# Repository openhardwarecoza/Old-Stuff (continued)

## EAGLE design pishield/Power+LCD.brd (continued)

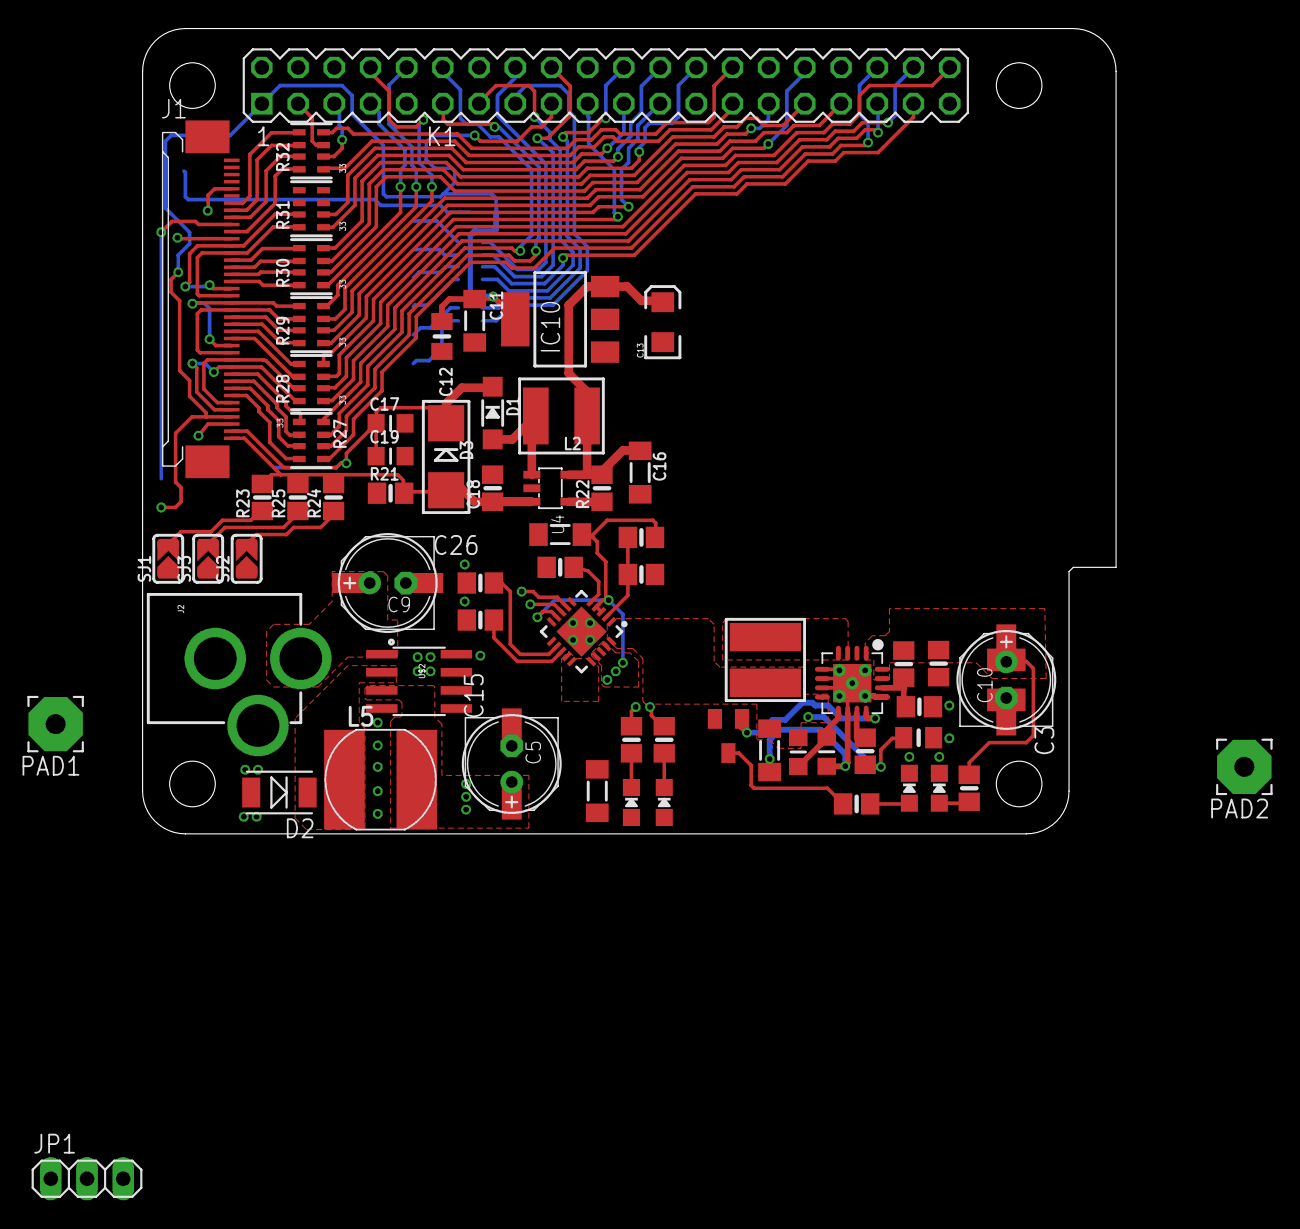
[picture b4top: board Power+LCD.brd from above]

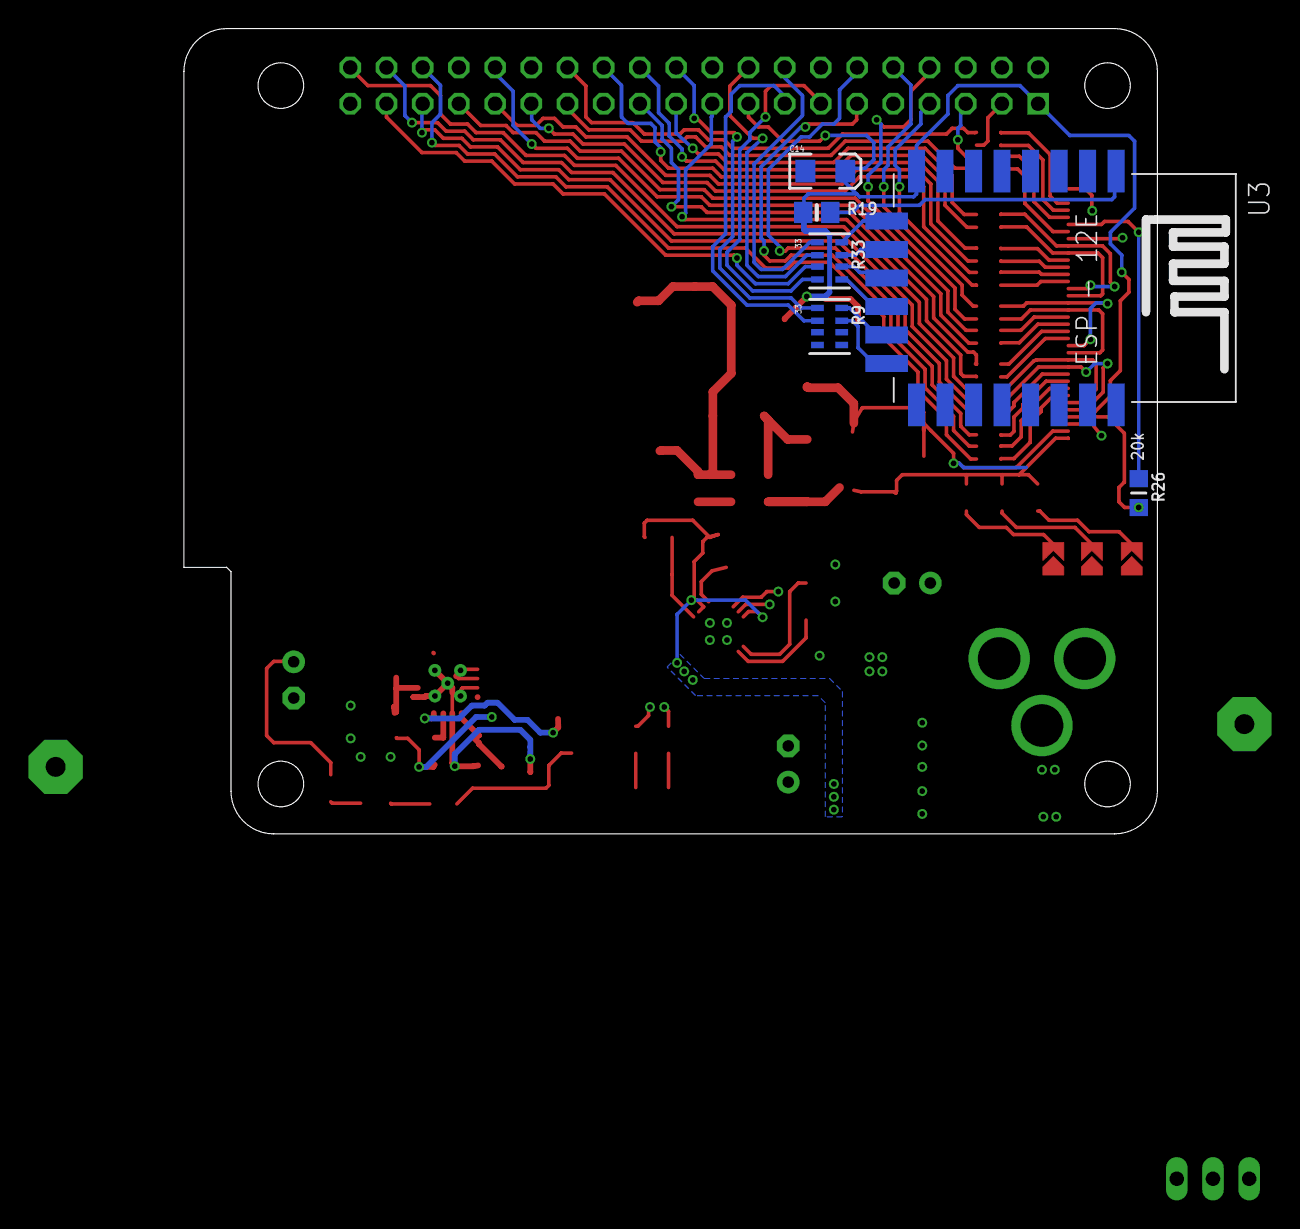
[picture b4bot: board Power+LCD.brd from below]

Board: 2 copper layers, 68.3 x 56.5 mm, 75 parts (6 on the bottom side), 90 nets.

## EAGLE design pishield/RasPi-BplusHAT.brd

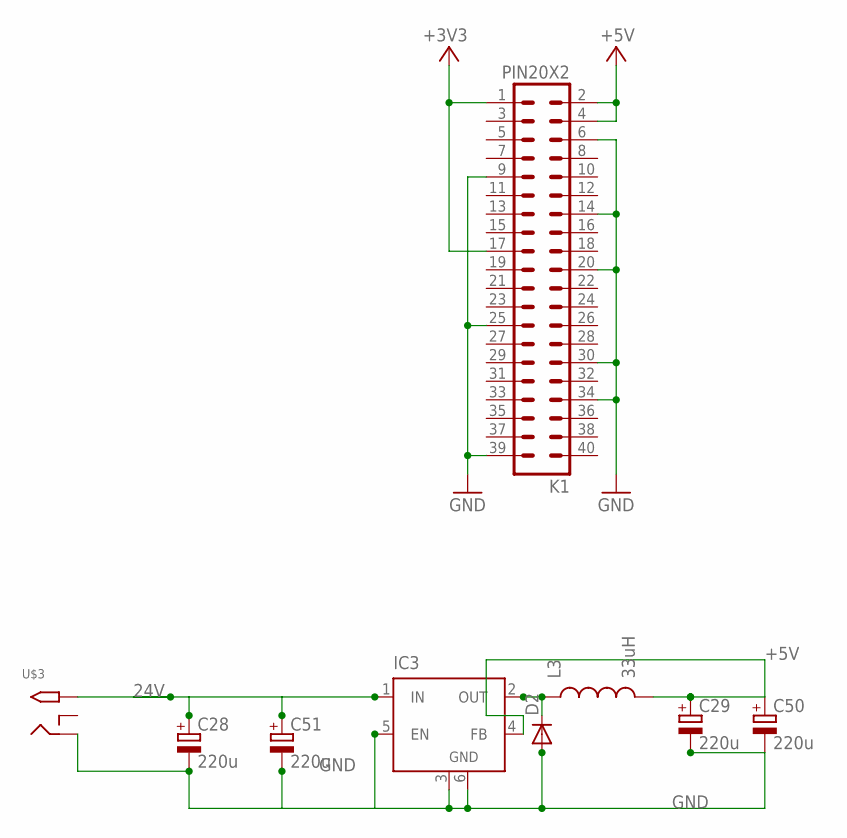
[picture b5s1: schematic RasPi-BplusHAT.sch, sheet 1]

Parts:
C28, C29: 220u; E2,5-7
C50, C51: 220u; PANASONIC_D
D2: DIODE-DO-214AC; DO-214AC
IC3: LM2596S; TO263-5
K1: PIN20X2; PIN_20X2
L3: 33uH; CDRH125
U$3: 2.1MMJACKTHM; PJ-102A

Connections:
24V: C28.+, C51.+, IC3.1 (IN), U$3.TIP
+3V3: K1.1, K1.17
+5V: C29.+, C50.+, IC3.4 (FB), K1.2, K1.4, L3.2
GND: C28.-, C29.-, C50.-, C51.-, D2.2 (A), IC3.3 (GND), IC3.5 (EN), IC3.6 (GND), K1.6, K1.9, K1.14, K1.20, K1.25, K1.30, K1.34, K1.39, U$3.RING
unnamed: D2.1 (C), IC3.2 (OUT), L3.1

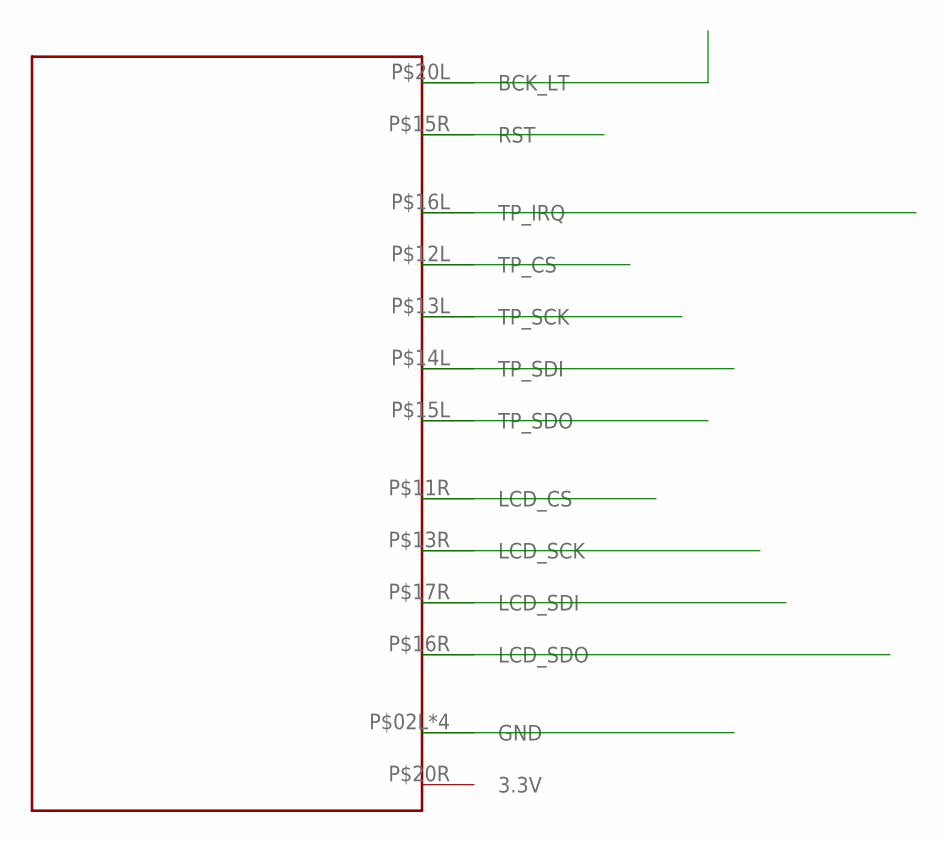
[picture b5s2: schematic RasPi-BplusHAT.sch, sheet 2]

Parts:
U$1: HY28BSTD; HY28B

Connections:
unnamed: U$1.P$02L (GND), U$1.P$02R (GND), U$1.P$19L (GND), U$1.P$19R (GND)

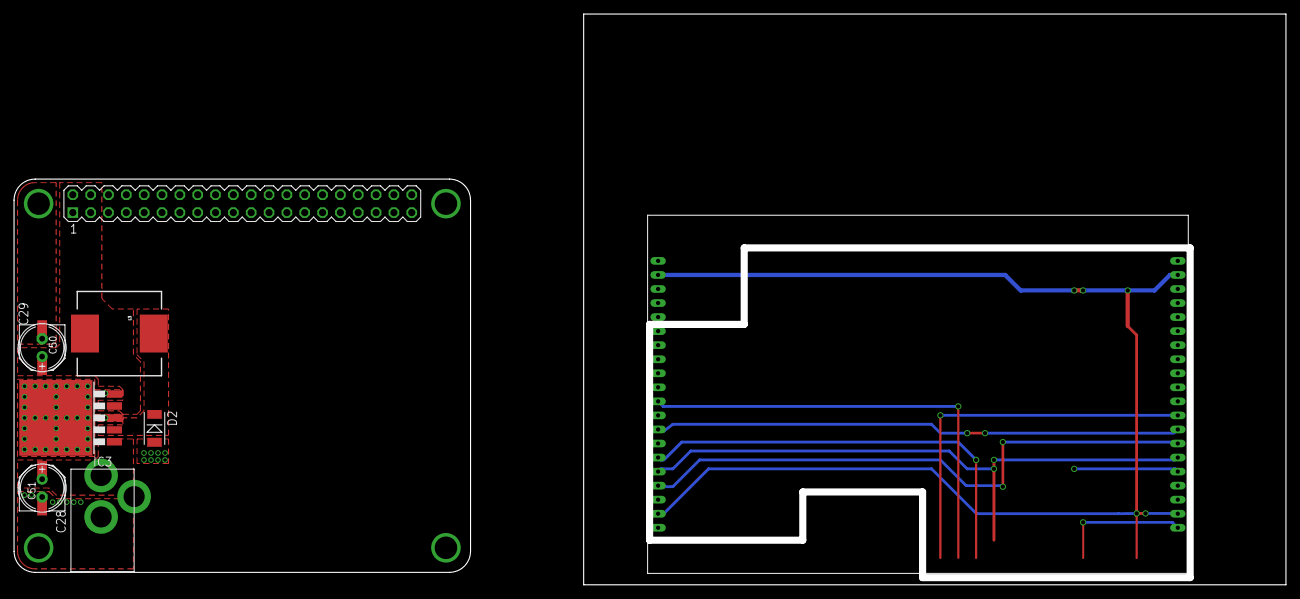
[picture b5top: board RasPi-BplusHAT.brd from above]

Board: 2 copper layers, 65.0 x 56.0 mm, 10 parts (0 on the bottom side), 6 nets.

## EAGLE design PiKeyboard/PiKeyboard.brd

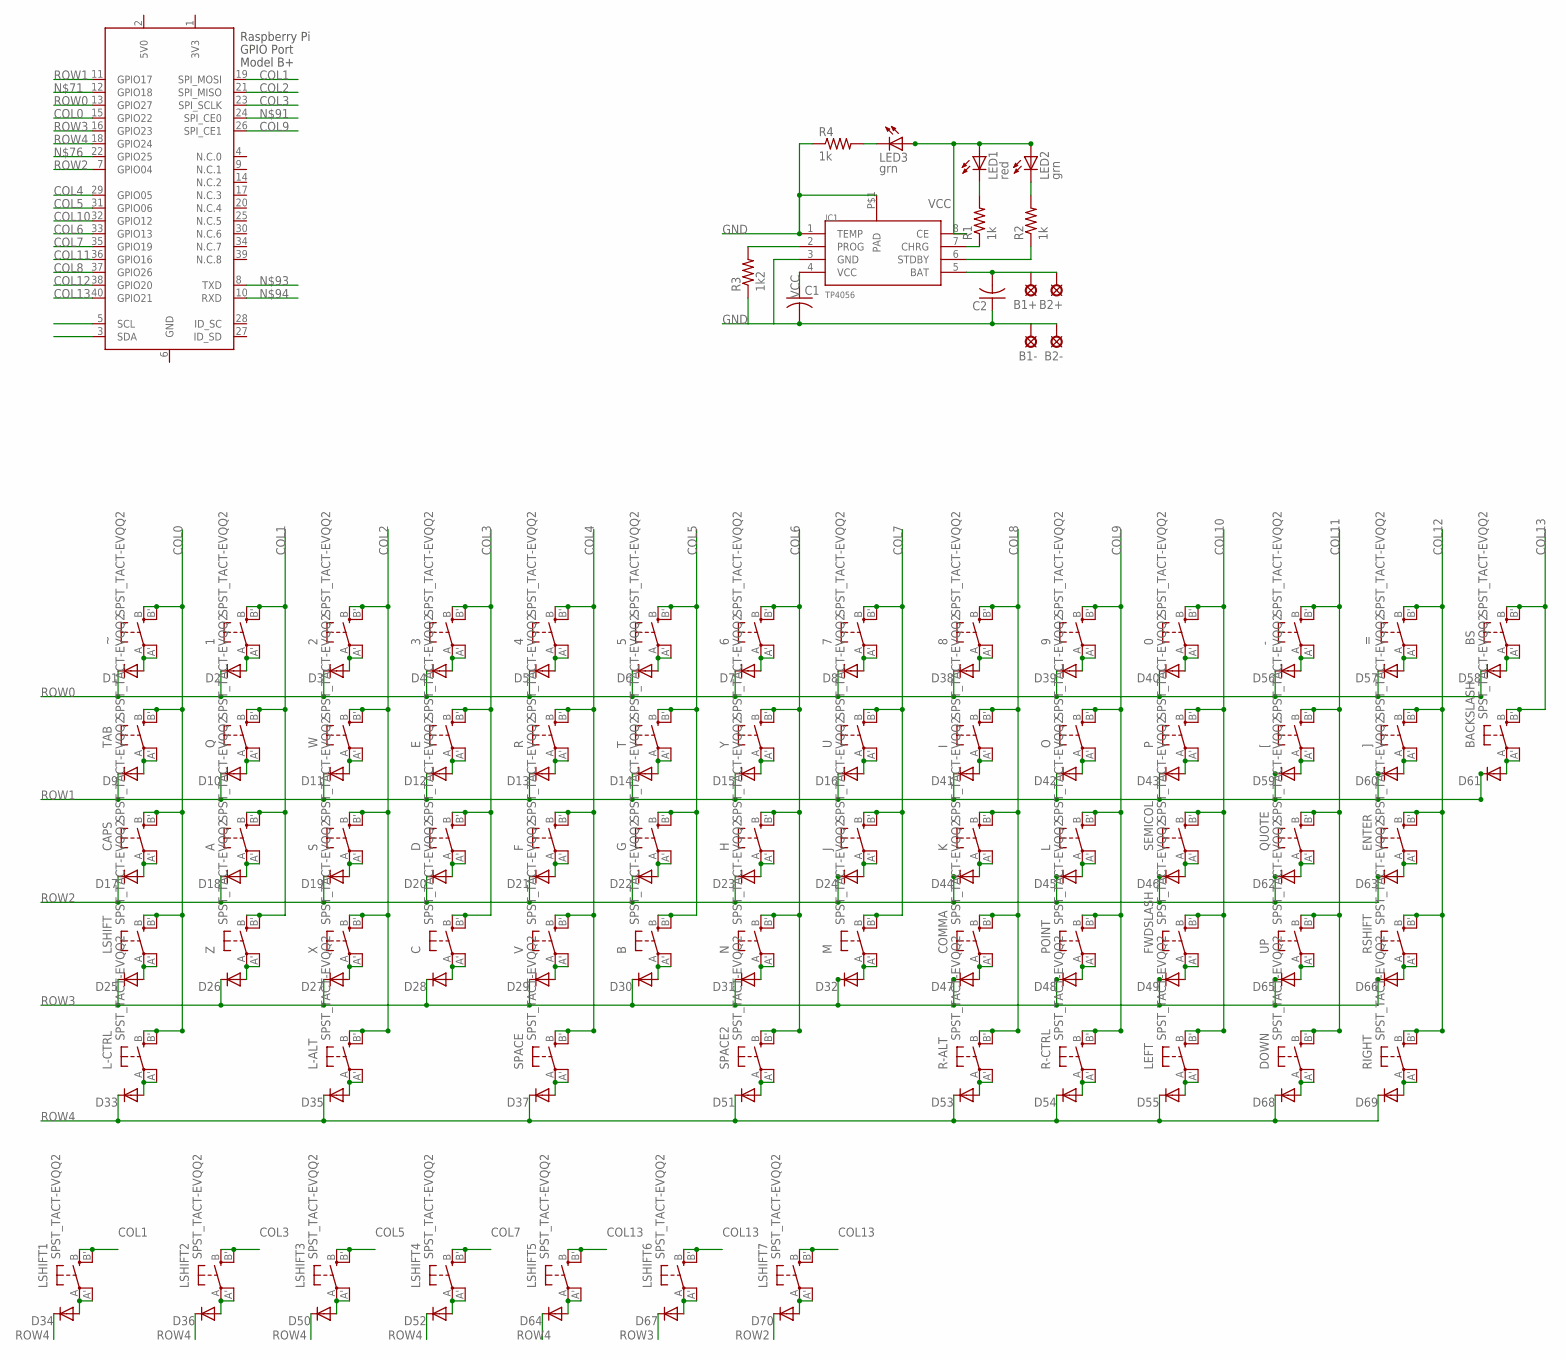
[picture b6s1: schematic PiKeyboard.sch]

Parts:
0, 1, 2, 3, 4, 5, 6, 7, 8, 9: SPST_TACT-EVQQ2; EVQ-Q2
-: SPST_TACT-EVQQ2; EVQ-Q2
=: SPST_TACT-EVQQ2; EVQ-Q2
A: SPST_TACT-EVQQ2; EVQ-Q2
B: SPST_TACT-EVQQ2; EVQ-Q2
B1+, B1-, B2+, B2-: SE14
BACKSLASH: SPST_TACT-EVQQ2; EVQ-Q2
BS: SPST_TACT-EVQQ2; EVQ-Q2
C: SPST_TACT-EVQQ2; EVQ-Q2
C1, C2: C-USC1206K; C1206K
CAPS: SPST_TACT-EVQQ2; EVQ-Q2
COMMA: SPST_TACT-EVQQ2; EVQ-Q2
D: SPST_TACT-EVQQ2; EVQ-Q2
D1, D2, D3, D4, D5, D6, D7, D8, D9, D10, D11, D12, D13, D14, D15, D16, D17, D18, D19, D20, D21, D22, D23, D24, D25, D26, D27, D28, D29, D30, D31, D32, D33, D34, D35, D36, D37, D38, D39, D40, D41, D42, D43, D44, D45, D46, D47, D48, D49, D50, D51, D52, D53, D54, D55, D56, D57, D58, D59, D60, D61, D62, D63, D64, D65, D66, D67, D68, D69, D70: DIODE-DO214AC; DO214AC
DOWN: SPST_TACT-EVQQ2; EVQ-Q2
E: SPST_TACT-EVQQ2; EVQ-Q2
ENTER: SPST_TACT-EVQQ2; EVQ-Q2
F: SPST_TACT-EVQQ2; EVQ-Q2
FWDSLASH: SPST_TACT-EVQQ2; EVQ-Q2
G: SPST_TACT-EVQQ2; EVQ-Q2
H: SPST_TACT-EVQQ2; EVQ-Q2
I: SPST_TACT-EVQQ2; EVQ-Q2
IC1: TP4056; SOP-8
J: SPST_TACT-EVQQ2; EVQ-Q2
K: SPST_TACT-EVQQ2; EVQ-Q2
L: SPST_TACT-EVQQ2; EVQ-Q2
L-ALT: SPST_TACT-EVQQ2; EVQ-Q2
L-CTRL: SPST_TACT-EVQQ2; EVQ-Q2
LED1: red; CHIPLED_1206
LED2, LED3: grn; CHIPLED_1206
LEFT: SPST_TACT-EVQQ2; EVQ-Q2
LSHIFT, LSHIFT1, LSHIFT2, LSHIFT3, LSHIFT4, LSHIFT5, LSHIFT6, LSHIFT7: SPST_TACT-EVQQ2; EVQ-Q2
M: SPST_TACT-EVQQ2; EVQ-Q2
N: SPST_TACT-EVQQ2; EVQ-Q2
O: SPST_TACT-EVQQ2; EVQ-Q2
P: SPST_TACT-EVQQ2; EVQ-Q2
POINT: SPST_TACT-EVQQ2; EVQ-Q2
Q: SPST_TACT-EVQQ2; EVQ-Q2
QUOTE: SPST_TACT-EVQQ2; EVQ-Q2
R: SPST_TACT-EVQQ2; EVQ-Q2
R1, R2, R4: 1k; M1206
R3: 1k2; M1206
R-ALT: SPST_TACT-EVQQ2; EVQ-Q2
R-CTRL: SPST_TACT-EVQQ2; EVQ-Q2
RIGHT: SPST_TACT-EVQQ2; EVQ-Q2
RSHIFT: SPST_TACT-EVQQ2; EVQ-Q2
S: SPST_TACT-EVQQ2; EVQ-Q2
SEMICOL: SPST_TACT-EVQQ2; EVQ-Q2
SPACE, SPACE2: SPST_TACT-EVQQ2; EVQ-Q2
T: SPST_TACT-EVQQ2; EVQ-Q2
TAB: SPST_TACT-EVQQ2; EVQ-Q2
U: SPST_TACT-EVQQ2; EVQ-Q2
UP: SPST_TACT-EVQQ2; EVQ-Q2
V: SPST_TACT-EVQQ2; EVQ-Q2
W: SPST_TACT-EVQQ2; EVQ-Q2
X: SPST_TACT-EVQQ2; EVQ-Q2
X1: RASPI_BOARD_B+_F; RASPI_BOARD_B+_FULL
Y: SPST_TACT-EVQQ2; EVQ-Q2
Z: SPST_TACT-EVQQ2; EVQ-Q2
[: SPST_TACT-EVQQ2; EVQ-Q2
]: SPST_TACT-EVQQ2; EVQ-Q2
~: SPST_TACT-EVQQ2; EVQ-Q2

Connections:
3V3: X1.1 (3V3)
5V0: X1.2 (5V0)
BATT+: B1+.MP, B2+.MP, C2.2, IC1.5 (BAT)
CHGLED: IC1.7 (CHRG), R1.1
CHRG: LED1.C, R1.2
COL0: CAPS.B (S), CAPS.B' (S1), L-CTRL.B (S), L-CTRL.B' (S1), LSHIFT.B (S), LSHIFT.B' (S1), TAB.B (S), TAB.B' (S1), X1.15 (GPIO22), ~.B (S), ~.B' (S1)
COL1: 1.B (S), 1.B' (S1), A.B (S), A.B' (S1), LSHIFT1.B (S), LSHIFT1.B' (S1), Q.B (S), Q.B' (S1), X1.19 (SPI_MOSI), Z.B (S), Z.B' (S1)
COL2: 2.B (S), 2.B' (S1), L-ALT.B (S), L-ALT.B' (S1), S.B (S), S.B' (S1), W.B (S), W.B' (S1), X.B (S), X.B' (S1), X1.21 (SPI_MISO)
COL3: 3.B (S), 3.B' (S1), C.B (S), C.B' (S1), D.B (S), D.B' (S1), E.B (S), E.B' (S1), LSHIFT2.B (S), LSHIFT2.B' (S1), X1.23 (SPI_SCLK)
COL4: 4.B (S), 4.B' (S1), F.B (S), F.B' (S1), R.B (S), R.B' (S1), SPACE.B (S), SPACE.B' (S1), V.B (S), V.B' (S1), X1.29 (GPIO05)
COL5: 5.B (S), 5.B' (S1), B.B (S), B.B' (S1), G.B (S), G.B' (S1), LSHIFT3.B (S), LSHIFT3.B' (S1), T.B (S), T.B' (S1), X1.31 (GPIO06)
COL6: 6.B (S), 6.B' (S1), H.B (S), H.B' (S1), N.B (S), N.B' (S1), SPACE2.B (S), SPACE2.B' (S1), X1.33 (GPIO13), Y.B (S), Y.B' (S1)
COL7: 7.B (S), 7.B' (S1), J.B (S), J.B' (S1), LSHIFT4.B (S), LSHIFT4.B' (S1), M.B (S), M.B' (S1), U.B (S), U.B' (S1), X1.35 (GPIO19)
COL8: 8.B (S), 8.B' (S1), COMMA.B (S), COMMA.B' (S1), I.B (S), I.B' (S1), K.B (S), K.B' (S1), R-ALT.B (S), R-ALT.B' (S1), X1.37 (GPIO26)
COL9: 9.B (S), 9.B' (S1), L.B (S), L.B' (S1), O.B (S), O.B' (S1), POINT.B (S), POINT.B' (S1), R-CTRL.B (S), R-CTRL.B' (S1), X1.26 (SPI_CE1)
COL10: 0.B (S), 0.B' (S1), FWDSLASH.B (S), FWDSLASH.B' (S1), LEFT.B (S), LEFT.B' (S1), P.B (S), P.B' (S1), SEMICOL.B (S), SEMICOL.B' (S1), X1.32 (GPIO12)
COL11: -.B (S), -.B' (S1), DOWN.B (S), DOWN.B' (S1), QUOTE.B (S), QUOTE.B' (S1), UP.B (S), UP.B' (S1), X1.36 (GPIO16), [.B (S), [.B' (S1)
COL12: =.B (S), =.B' (S1), ENTER.B (S), ENTER.B' (S1), RIGHT.B (S), RIGHT.B' (S1), RSHIFT.B (S), RSHIFT.B' (S1), X1.38 (GPIO20), ].B (S), ].B' (S1)
COL13: BACKSLASH.B (S), BACKSLASH.B' (S1), BS.B (S), BS.B' (S1), LSHIFT5.B (S), LSHIFT5.B' (S1), LSHIFT6.B (S), LSHIFT6.B' (S1), LSHIFT7.B (S), LSHIFT7.B' (S1), X1.40 (GPIO21)
GND: B1-.MP, B2-.MP, C1.2, C2.1, IC1.1 (TEMP), IC1.3 (GND), IC1.P$1 (PAD), R3.1, R4.1, X1.6 (GND)
unnamed: D1.A, ~.A, ~.A' (P1)
unnamed: 1.A, 1.A' (P1), D2.A
unnamed: 2.A, 2.A' (P1), D3.A
unnamed: 3.A, 3.A' (P1), D4.A
unnamed: 4.A, 4.A' (P1), D5.A
unnamed: 5.A, 5.A' (P1), D6.A
unnamed: 6.A, 6.A' (P1), D7.A
unnamed: 7.A, 7.A' (P1), D8.A
unnamed: D9.A, TAB.A, TAB.A' (P1)
unnamed: D10.A, Q.A, Q.A' (P1)
unnamed: D11.A, W.A, W.A' (P1)
unnamed: D12.A, E.A, E.A' (P1)
unnamed: D13.A, R.A, R.A' (P1)
unnamed: D14.A, T.A, T.A' (P1)
unnamed: D15.A, Y.A, Y.A' (P1)
unnamed: D16.A, U.A, U.A' (P1)
unnamed: CAPS.A, CAPS.A' (P1), D17.A
unnamed: A.A, A.A' (P1), D18.A
unnamed: D19.A, S.A, S.A' (P1)
unnamed: D.A, D.A' (P1), D20.A
unnamed: D21.A, F.A, F.A' (P1)
unnamed: D22.A, G.A, G.A' (P1)
unnamed: D23.A, H.A, H.A' (P1)
unnamed: D24.A, J.A, J.A' (P1)
unnamed: D25.A, LSHIFT.A, LSHIFT.A' (P1)
unnamed: D26.A, Z.A, Z.A' (P1)
unnamed: D27.A, X.A, X.A' (P1)
unnamed: C.A, C.A' (P1), D28.A
unnamed: D29.A, V.A, V.A' (P1)
unnamed: B.A, B.A' (P1), D30.A
unnamed: D31.A, N.A, N.A' (P1)
unnamed: D32.A, M.A, M.A' (P1)
unnamed: D33.A, L-CTRL.A, L-CTRL.A' (P1)
unnamed: D34.A, LSHIFT1.A, LSHIFT1.A' (P1)
unnamed: D36.A, LSHIFT2.A, LSHIFT2.A' (P1)
unnamed: D50.A, LSHIFT3.A, LSHIFT3.A' (P1)
unnamed: D37.A, SPACE.A, SPACE.A' (P1)
unnamed: 8.A, 8.A' (P1), D38.A
unnamed: 9.A, 9.A' (P1), D39.A
unnamed: 0.A, 0.A' (P1), D40.A
unnamed: D41.A, I.A, I.A' (P1)
unnamed: D42.A, O.A, O.A' (P1)
unnamed: D43.A, P.A, P.A' (P1)
unnamed: D44.A, K.A, K.A' (P1)
unnamed: D45.A, L.A, L.A' (P1)
unnamed: D46.A, SEMICOL.A, SEMICOL.A' (P1)
unnamed: COMMA.A, COMMA.A' (P1), D47.A
unnamed: D48.A, POINT.A, POINT.A' (P1)
unnamed: D49.A, FWDSLASH.A, FWDSLASH.A' (P1)
unnamed: D52.A, LSHIFT4.A, LSHIFT4.A' (P1)
unnamed: D51.A, SPACE2.A, SPACE2.A' (P1)
unnamed: D64.A, LSHIFT5.A, LSHIFT5.A' (P1)
unnamed: D53.A, R-ALT.A, R-ALT.A' (P1)
unnamed: D54.A, R-CTRL.A, R-CTRL.A' (P1)
unnamed: D55.A, LEFT.A, LEFT.A' (P1)
unnamed: -.A, -.A' (P1), D56.A
unnamed: =.A, =.A' (P1), D57.A
unnamed: BS.A, BS.A' (P1), D58.A
unnamed: D59.A, [.A, [.A' (P1)
unnamed: D60.A, ].A, ].A' (P1)
unnamed: BACKSLASH.A, BACKSLASH.A' (P1), D61.A
unnamed: D62.A, QUOTE.A, QUOTE.A' (P1)
unnamed: D63.A, ENTER.A, ENTER.A' (P1)
unnamed: D67.A, LSHIFT6.A, LSHIFT6.A' (P1)
unnamed: D65.A, UP.A, UP.A' (P1)
unnamed: D66.A, RSHIFT.A, RSHIFT.A' (P1)
unnamed: D70.A, LSHIFT7.A, LSHIFT7.A' (P1)
unnamed: D68.A, DOWN.A, DOWN.A' (P1)
unnamed: D69.A, RIGHT.A, RIGHT.A' (P1)
unnamed: LED3.C, R4.2
PROG: IC1.2 (PROG), R3.2
ROW0: D1.C, D2.C, D3.C, D4.C, D5.C, D6.C, D7.C, D8.C, D38.C, D39.C, D40.C, D56.C, D57.C, D58.C, X1.13 (GPIO27)
ROW1: D9.C, D10.C, D11.C, D12.C, D13.C, D14.C, D15.C, D16.C, D41.C, D42.C, D43.C, D59.C, D60.C, D61.C, X1.11 (GPIO17)
ROW2: D17.C, D18.C, D19.C, D20.C, D21.C, D22.C, D23.C, D24.C, D44.C, D45.C, D46.C, D62.C, D63.C, D70.C, X1.7 (GPIO04)
ROW3: D25.C, D26.C, D27.C, D28.C, D29.C, D30.C, D31.C, D32.C, D47.C, D48.C, D49.C, D65.C, D66.C, D67.C, X1.16 (GPIO23)
ROW4: D33.C, D34.C, D35.C, D36.C, D37.C, D50.C, D51.C, D52.C, D53.C, D54.C, D55.C, D64.C, D68.C, D69.C, X1.18 (GPIO24)
SBYLED: IC1.6 (STDBY), R2.1
SPCEBAR: D35.A, L-ALT.A, L-ALT.A' (P1)
STANDBY: LED2.C, R2.2
VCC: C1.1, IC1.4 (VCC), IC1.8 (CE), LED1.A, LED2.A, LED3.A

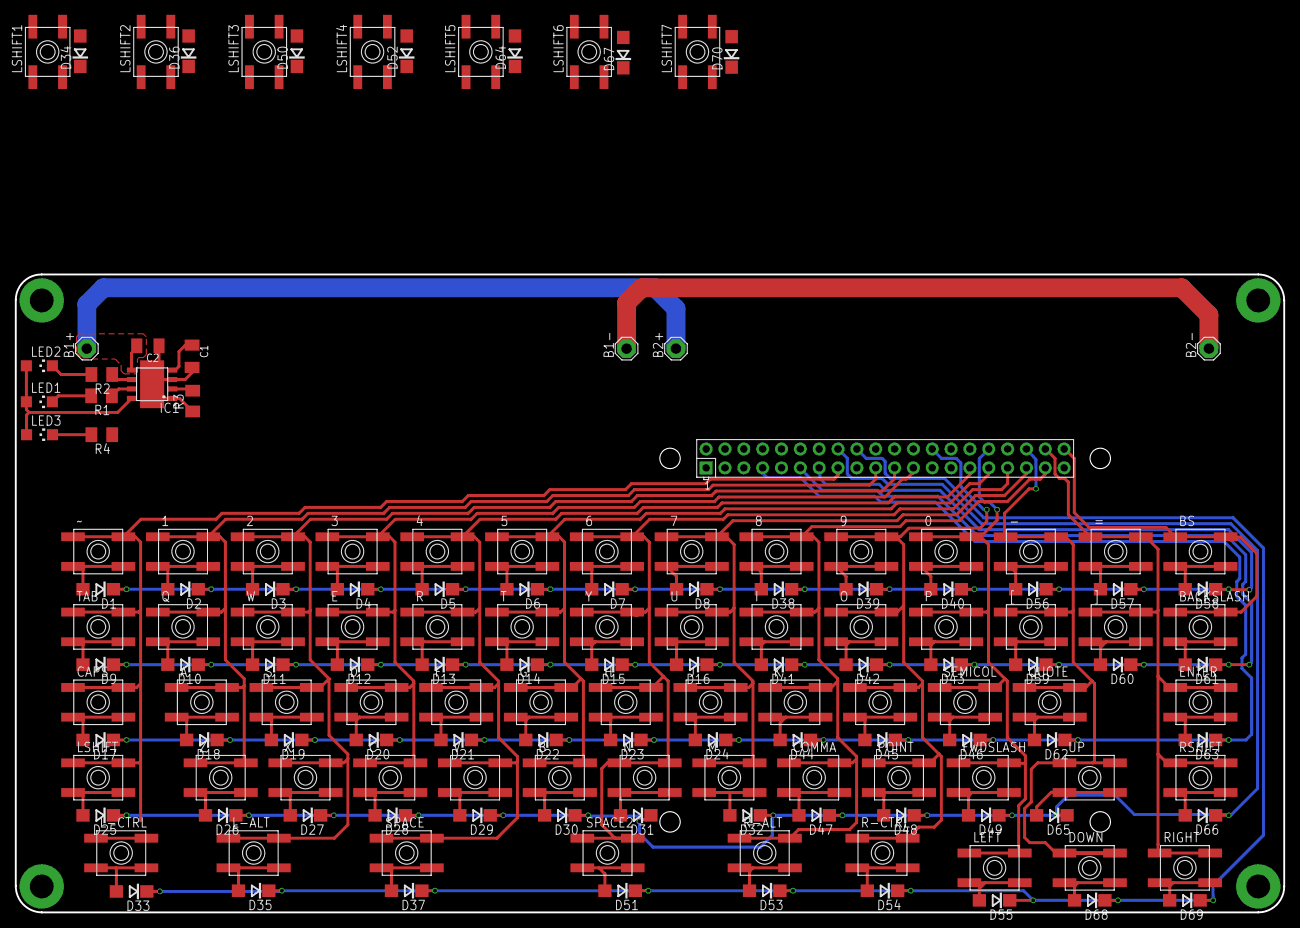
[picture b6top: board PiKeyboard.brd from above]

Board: 2 copper layers, 171.0 x 86.0 mm, 155 parts (0 on the bottom side), 98 nets.

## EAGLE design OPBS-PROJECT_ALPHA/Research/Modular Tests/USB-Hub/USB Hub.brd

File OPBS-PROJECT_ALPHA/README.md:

A secret project for OpenBuilds.com

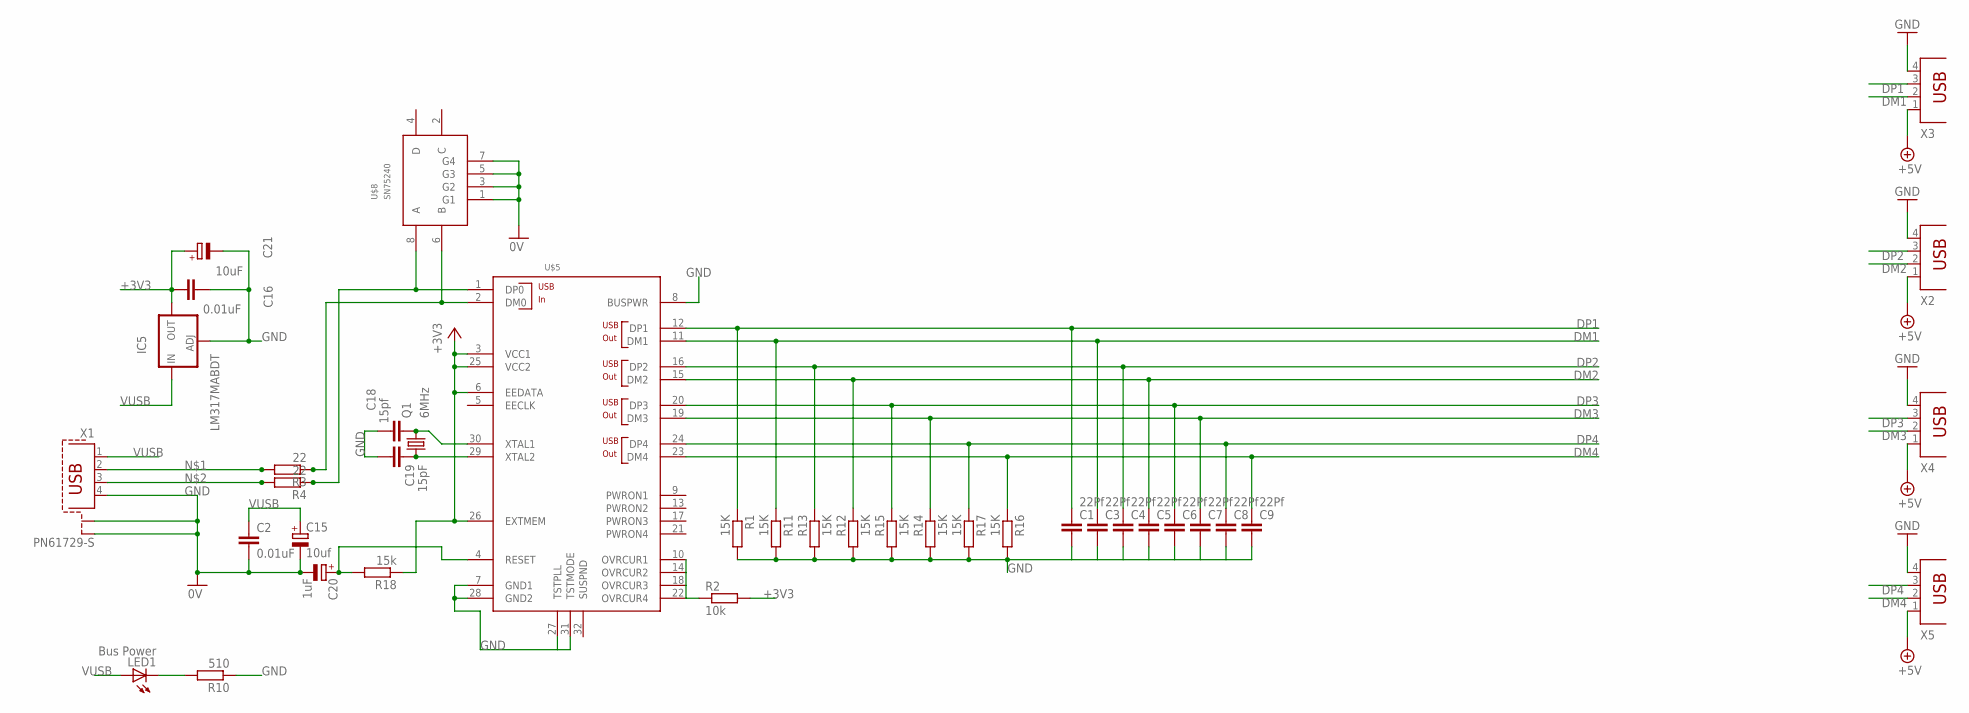
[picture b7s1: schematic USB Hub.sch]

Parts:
C1, C3, C4, C5, C6, C7, C8, C9: 22Pf; C0805
C2, C16: 0.01uF; C0805
C15: 10uf; E2,5-6
C18: 15pf; C0805
C19: 15pF; C0805
C20: 1uF; E2,5-6
C21: 10uF; E2,5-6
IC5: LM317MABDT; DPACK
LED1: Bus Power; CHIP-LED0805
Q1: 6MHz; HC49UP
R1, R11, R12, R13, R14, R15, R16, R17: 15K; R0805
R2: 10k; R0805
R3, R4: 22; R0805
R10: 510; R0805
R18: 15k; R0805
U$5: TUSB2046; LQFP-32
U$8: SN75240; TSSOP8
X1: PN61729-S
X2, X3, X4, X5: PN87520

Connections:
+3V3: C16.1, C21.+, IC5.4 (OUT), R2.2, R18.1, U$5.3 (VCC1), U$5.6 (EEDATA), U$5.25 (VCC2), U$5.26 (EXTMEM)
DM0: R3.1, U$5.2 (DM0), U$8.6 (B)
DM1: C3.1, R11.1, U$5.11 (DM1), X3.2
DM2: C5.1, R12.1, U$5.15 (DM2), X2.2
DM3: C7.1, R14.1, U$5.19 (DM3), X4.2
DM4: C9.1, R16.1, U$5.23 (DM4), X5.2
DP0: R4.1, U$5.1 (DP0), U$8.8 (A)
DP1: C1.1, R1.1, U$5.12 (DP1), X3.3
DP2: C4.1, R13.1, U$5.16 (DP2), X2.3
DP3: C6.1, R15.1, U$5.20 (DP3), X4.3
DP4: C8.1, R17.1, U$5.24 (DP4), X5.3
GND: C1.2, C2.2, C3.2, C4.2, C5.2, C6.2, C7.2, C8.2, C9.2, C15.-, C16.2, C18.1, C19.2, C20.-, C21.-, IC5.1 (ADJ), R1.2, R10.1, R11.2, R12.2, R13.2, R14.2, R15.2, R16.2, R17.2, U$5.7 (GND1), U$5.8 (BUSPWR), U$5.27 (TSTPLL), U$5.28 (GND2), U$5.31 (TSTMODE), U$8.1 (G1), U$8.3 (G2), U$8.5 (G3), U$8.7 (G4), X1.4, X1.S1, X1.S2, X2.4, X3.4, X4.4, X5.4
LEDV: LED1.C, R10.2
unnamed: R3.2, X1.2
unnamed: R4.2, X1.3
unnamed: R2.1, U$5.10 (OVRCUR1), U$5.14 (OVRCUR2), U$5.18 (OVRCUR3), U$5.22 (OVRCUR4)
RESET: C20.+, R18.2, U$5.4 (RESET)
VCC: X2.1, X3.1, X4.1, X5.1
VUSB: C2.1, C15.+, IC5.3 (IN), LED1.A, X1.1
XTAL1: C18.2, Q1.2, U$5.30 (XTAL1)
XTAL2: C19.1, Q1.1, U$5.29 (XTAL2)

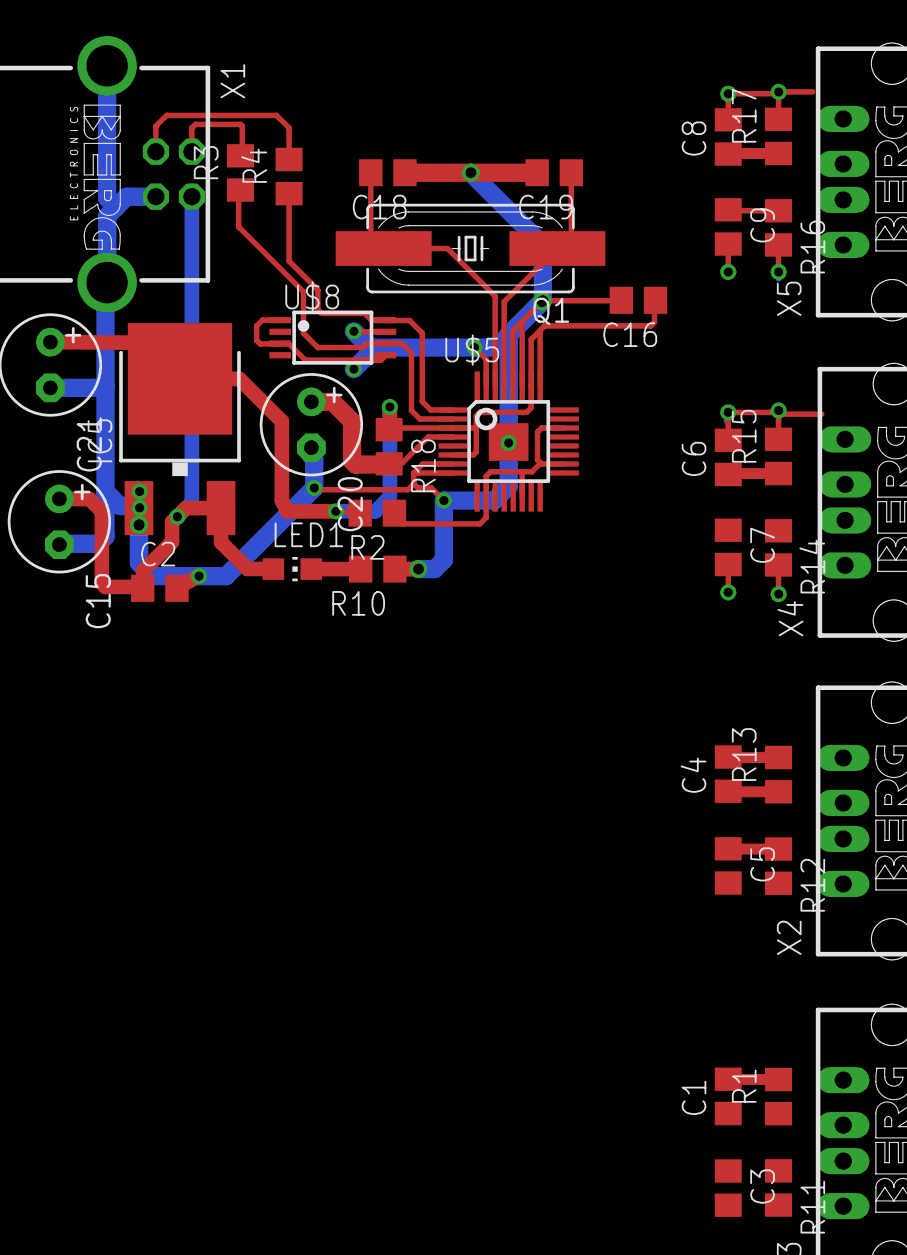
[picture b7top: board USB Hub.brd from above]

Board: 2 copper layers, 38 parts (0 on the bottom side), 21 nets.

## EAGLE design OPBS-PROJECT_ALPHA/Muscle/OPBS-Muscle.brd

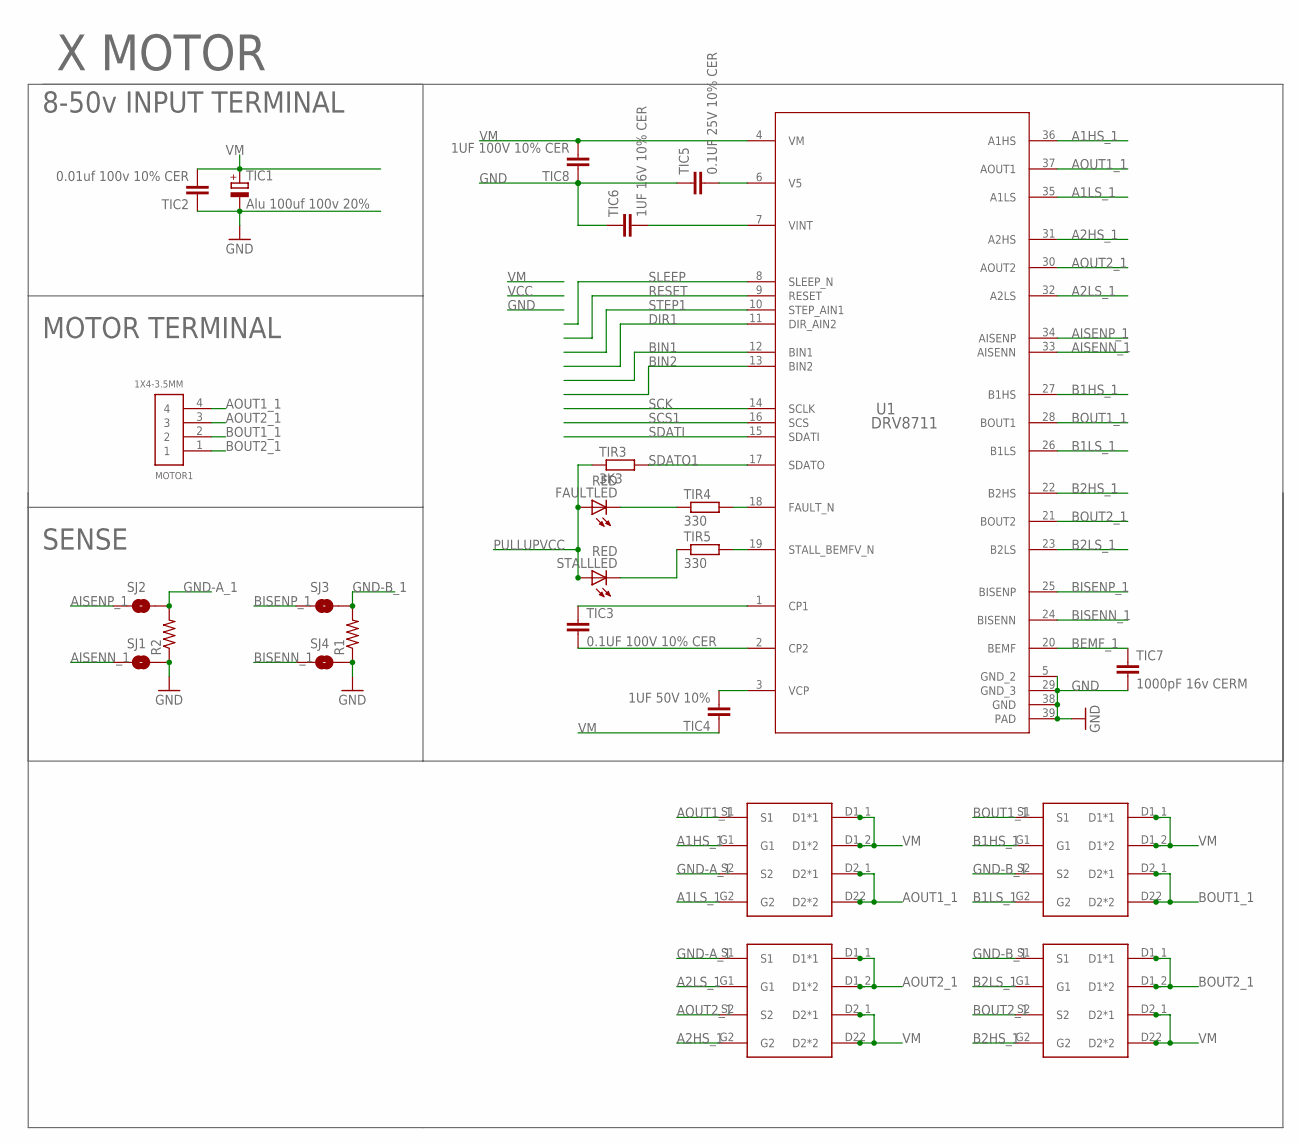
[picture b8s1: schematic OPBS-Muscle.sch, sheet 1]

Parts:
FAULTLED: RED; 1206
MOTOR1: 1X4-3.5MM; 1X04-3.5MM
R1, R2: R-US_R2512; R2512
SJ1, SJ2, SJ3, SJ4: SOLDERJUMPERTRACE; SJ_2S-TRACE
STALLLED: RED; 1206
TIC1: Alu 100uf 100v 20%; E5-10,5
TIC2: 0.01uf 100v 10% CER; C0603K
TIC3: 0.1UF 100V 10% CER; C0603K
TIC4: 1UF 50V 10%; C0805K
TIC5: 0.1UF 25V 10% CER; C0603K
TIC6: 1UF 16V 10% CER; C0603K
TIC7: 1000pF 16v CERM; C0603K
TIC8: 1UF 100V 10% CER; C1206K
TIR3: 3K3; R1206
TIR4, TIR5: 330; R1206
U1: DRV8711; DCP0038A_N
U$1, U$2, U$3, U$4: CSD88537ND

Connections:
A1HS_1: U1.36 (A1HS), U$1.G1
A1LS_1: U1.35 (A1LS), U$1.G2
A2HS_1: U1.31 (A2HS), U$3.G2
A2LS_1: U1.32 (A2LS), U$3.G1
AISENN_1: SJ1.1, U1.33 (AISENN)
AISENP_1: SJ2.1, U1.34 (AISENP)
AOUT1_1: MOTOR1.4, U1.37 (AOUT1), U$1.D2_1 (D2*1), U$1.D22 (D2*2), U$1.S1
AOUT2_1: MOTOR1.3, U1.30 (AOUT2), U$3.D1_1 (D1*1), U$3.D1_2 (D1*2), U$3.S2
B1HS_1: U1.27 (B1HS), U$2.G1
B1LS_1: U1.26 (B1LS), U$2.G2
B2HS_1: U1.22 (B2HS), U$4.G2
B2LS_1: U1.23 (B2LS), U$4.G1
BEMF_1: TIC7.1, U1.20 (BEMF)
BIN1: U1.12 (BIN1)
BIN2: U1.13 (BIN2)
BISENN_1: SJ4.1, U1.24 (BISENN)
BISENP_1: SJ3.1, U1.25 (BISENP)
BOUT1_1: MOTOR1.2, U1.28 (BOUT1), U$2.D2_1 (D2*1), U$2.D22 (D2*2), U$2.S1
BOUT2_1: MOTOR1.1, U1.21 (BOUT2), U$4.D1_1 (D1*1), U$4.D1_2 (D1*2), U$4.S2
CP1_1: TIC3.1, U1.1 (CP1)
CP2_1: TIC3.2, U1.2 (CP2)
DIR1: U1.11 (DIR_AIN2); also elsewhere on the board
FAULTLED: FAULTLED.C, TIR4.1
FAULT_N1: TIR4.2, U1.18 (FAULT_N)
GND: R1.1, R2.1, SJ1.2, SJ4.2, TIC1.-, TIC2.1, TIC5.1, TIC6.1, TIC7.2, TIC8.1, U1.5 (GND_2), U1.29 (GND_3), U1.38 (GND), U1.39 (PAD); also elsewhere on the board
GND-A_1: R2.2, SJ2.2, U$1.S2, U$3.S1
GND-B_1: R1.2, SJ3.2, U$2.S2, U$4.S1
PULLUPVCC: FAULTLED.A, STALLLED.A, TIR3.1; also elsewhere on the board
RESET: U1.9 (RESET); also elsewhere on the board
SCK: U1.14 (SCLK); also elsewhere on the board
SCS1: U1.16 (SCS); also elsewhere on the board
SDATI: U1.15 (SDATI); also elsewhere on the board
SDATO1: TIR3.2, U1.17 (SDATO); also elsewhere on the board
SLEEP: U1.8 (SLEEP_N); also elsewhere on the board
STALLLED: STALLLED.C, TIR5.1
STALL_N1: TIR5.2, U1.19 (STALL_BEMFV_N)
STEP1: U1.10 (STEP_AIN1); also elsewhere on the board
V5_1: TIC5.2, U1.6 (V5)
VCP1: TIC4.2, U1.3 (VCP)
VINT1: TIC6.2, U1.7 (VINT)
VM: TIC1.+, TIC2.2, TIC4.1, TIC8.2, U1.4 (VM), U$1.D1_1 (D1*1), U$1.D1_2 (D1*2), U$2.D1_1 (D1*1), U$2.D1_2 (D1*2), U$3.D2_1 (D2*1), U$3.D22 (D2*2), U$4.D2_1 (D2*1), U$4.D22 (D2*2); also elsewhere on the board

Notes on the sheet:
8-50v INPUT TERMINAL
MOTOR TERMINAL
SENSE
X MOTOR
